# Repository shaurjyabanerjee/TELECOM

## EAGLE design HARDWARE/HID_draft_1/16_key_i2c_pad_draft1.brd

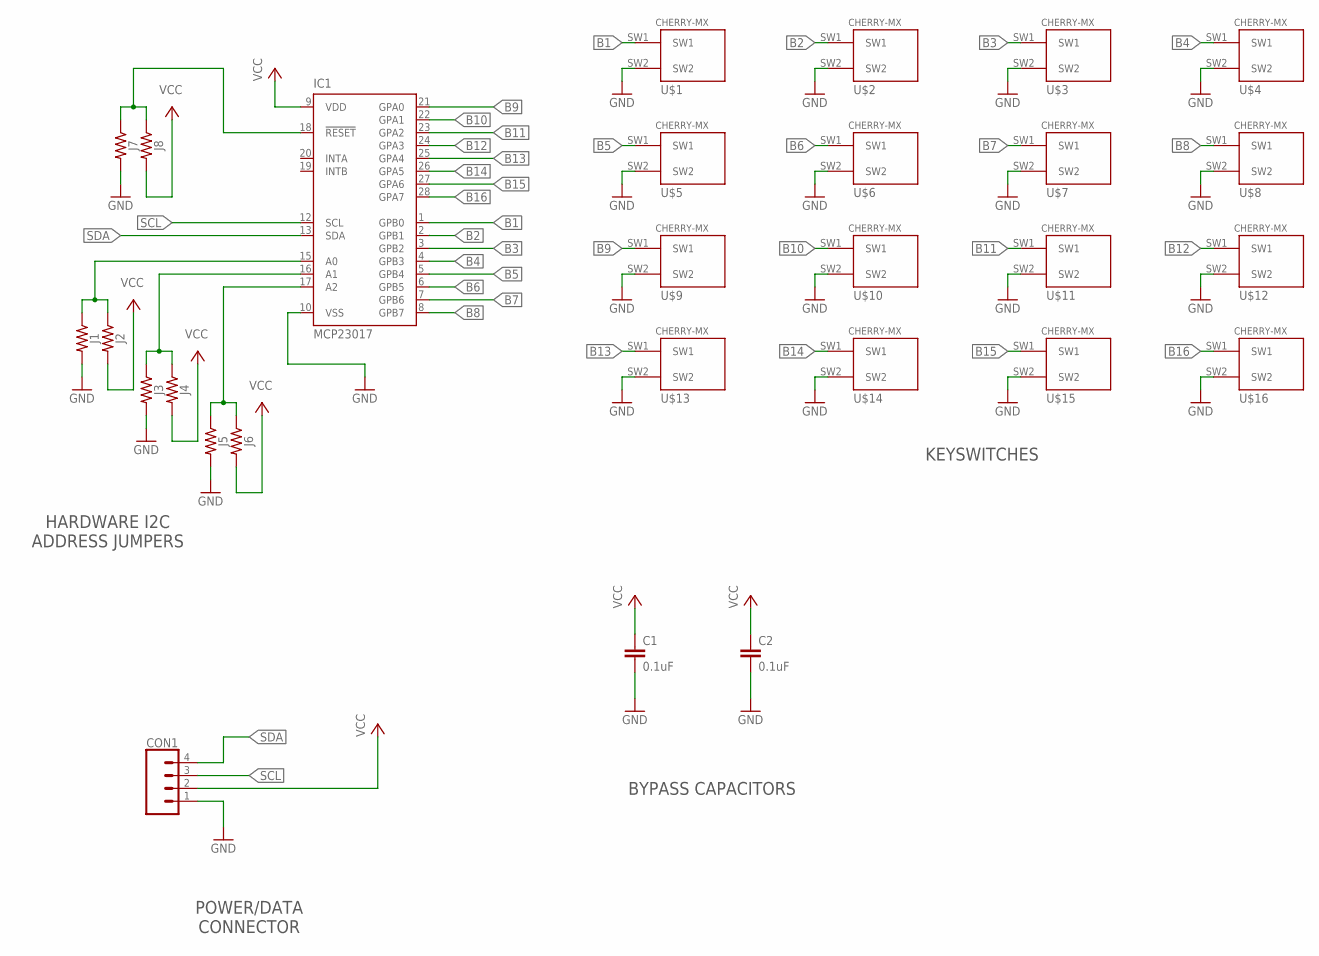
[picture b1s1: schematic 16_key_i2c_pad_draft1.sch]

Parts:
C1, C2: 0.1uF; CAP-PTH-SMALL-KIT
CON1: CONN_04; 1X04
IC1: MCP23017; DIL28-3
J1, J2, J3, J4, J5, J6, J7, J8: 0805
U$1, U$2, U$3, U$4, U$5, U$6, U$7, U$8, U$9, U$10, U$11, U$12, U$13, U$14, U$15, U$16: CHERRY-MXSTANDARD; CHERRY-MX

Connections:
B1: IC1.1 (GPB0), U$1.SW1
B2: IC1.2 (GPB1), U$2.SW1
B3: IC1.3 (GPB2), U$3.SW1
B4: IC1.4 (GPB3), U$4.SW1
B5: IC1.5 (GPB4), U$5.SW1
B6: IC1.6 (GPB5), U$6.SW1
B7: IC1.7 (GPB6), U$7.SW1
B8: IC1.8 (GPB7), U$8.SW1
B9: IC1.21 (GPA0), U$9.SW1
B10: IC1.22 (GPA1), U$10.SW1
B11: IC1.23 (GPA2), U$11.SW1
B12: IC1.24 (GPA3), U$12.SW1
B13: IC1.25 (GPA4), U$13.SW1
B14: IC1.26 (GPA5), U$14.SW1
B15: IC1.27 (GPA6), U$15.SW1
B16: IC1.28 (GPA7), U$16.SW1
GND: C1.2, C2.2, CON1.1, IC1.10 (VSS), J1.2, J3.2, J5.2, J7.2, U$1.SW2, U$2.SW2, U$3.SW2, U$4.SW2, U$5.SW2, U$6.SW2, U$7.SW2, U$8.SW2, U$9.SW2, U$10.SW2, U$11.SW2, U$12.SW2, U$13.SW2, U$14.SW2, U$15.SW2, U$16.SW2
unnamed: IC1.15 (A0), J1.1, J2.1
unnamed: IC1.16 (A1), J3.1, J4.1
unnamed: IC1.17 (A2), J5.1, J6.1
unnamed: IC1.18 (!RESET), J7.1, J8.1
SCL: CON1.3, IC1.12 (SCL)
SDA: CON1.4, IC1.13 (SDA)
VCC: C1.1, C2.1, CON1.2, IC1.9 (VDD), J2.2, J4.2, J6.2, J8.2

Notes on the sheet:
HARDWARE I2C ADDRESS JUMPERS
KEYSWITCHES
BYPASS CAPACITORS
POWER/DATA CONNECTOR

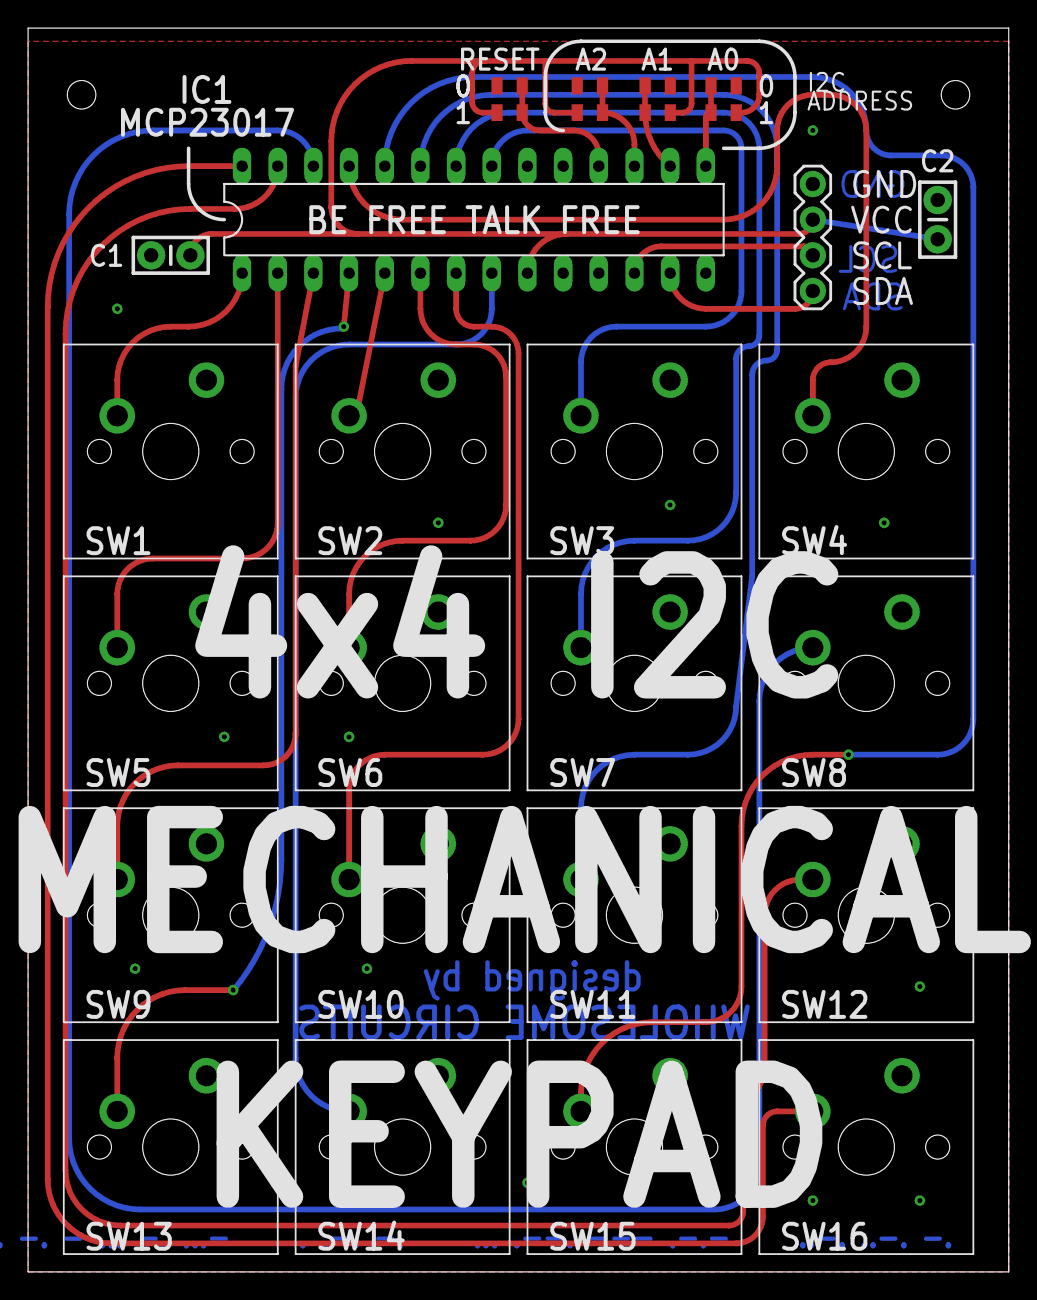
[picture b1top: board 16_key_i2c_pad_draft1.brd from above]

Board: 2 copper layers, 69.8 x 88.6 mm, 28 parts (0 on the bottom side), 24 nets.

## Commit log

2020-07-02 added directory for p5 network visualizer
2020-07-02 managed to pull in a map from mapbox
2020-07-07 wrote simple I2C keypad tester/visualizer

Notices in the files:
parts and their libraries:
SparkFun-Connectors: Licensing: Creative Commons ShareAlike 4.0 International - https://creativecommons.org/licenses/by-sa/4.0
